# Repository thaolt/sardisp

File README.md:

# sardisp

## Content

  * [What is it?](#what-is-it)
  * [Installation](#installation)
    + [Windows](#windows)
    + [Linux](#linux)
  * [How to use](#how-to-use)
    + [avrdude](#avrdude)
    + [AVRDUDESS](#avrdudess)
    + [Arduino IDE](#arduino-ide)
  * [Tools](#tools)
  * [Schematic](#schematic)
  * [Perf-board implement](#perf-board-implement)
  * [References](#references)

## What is it?

DIY Simple Arduino In-System-Programmer (aka perf-board USBasp clone)

## Installation

### Windows

**Driver installation**

Please read:

* https://zadig.akeo.ie/
* https://electronics.stackexchange.com/questions/416714/avrdude-does-not-recognize-usbasp-device/417509#417509

Or download:

https://raw.githubusercontent.com/thaolt/sardisp/master/drivers/usbasp_signed.zip

### Linux

Linux doesn't need driver installation

However, it would be more convenient to allow current user access USB instead of execute commands under `root` or `sudo`

If you ever run these steps before, they don't need to be executed again

`$USER` is your current login name on your machine

```
sudo adduser $USER dialout
sudo adduser $USER tty
sudo adduser $USER plugdev
```

Then log out of current desktop session and log in again, it's done.

## How to use

Any software / IDE support USBasp programmer

### avrdude

```
avrdude -u -c usbasp -P usb ...
```
### AVRDUDESS

### Arduino IDE

`Tools` > `Programmer` > `USBasp`

## Tools

* **Kicad PCB** software is used for making perf-board design easier. https://kicad.org/
* **AVRDUDESS** is a GUI software for avrdude for flashing the firmware, works on Windows, Mac, Linux. https://blog.zakkemble.net/avrdudess-a-gui-for-avrdude/

## Schematic

## Perf-board implement

## References

* https://www.fischl.de/usbasp/
* https://github.com/obdev/v-usb
* https://hackaday.io/project/27401-creative-repairs-and-hacks/log/156127-replacing-an-atmega8-with-a-atmega328p-on-a-usbasp-board
* https://tiktakx.wordpress.com/tag/diy-usbasp-using-atmega-328/

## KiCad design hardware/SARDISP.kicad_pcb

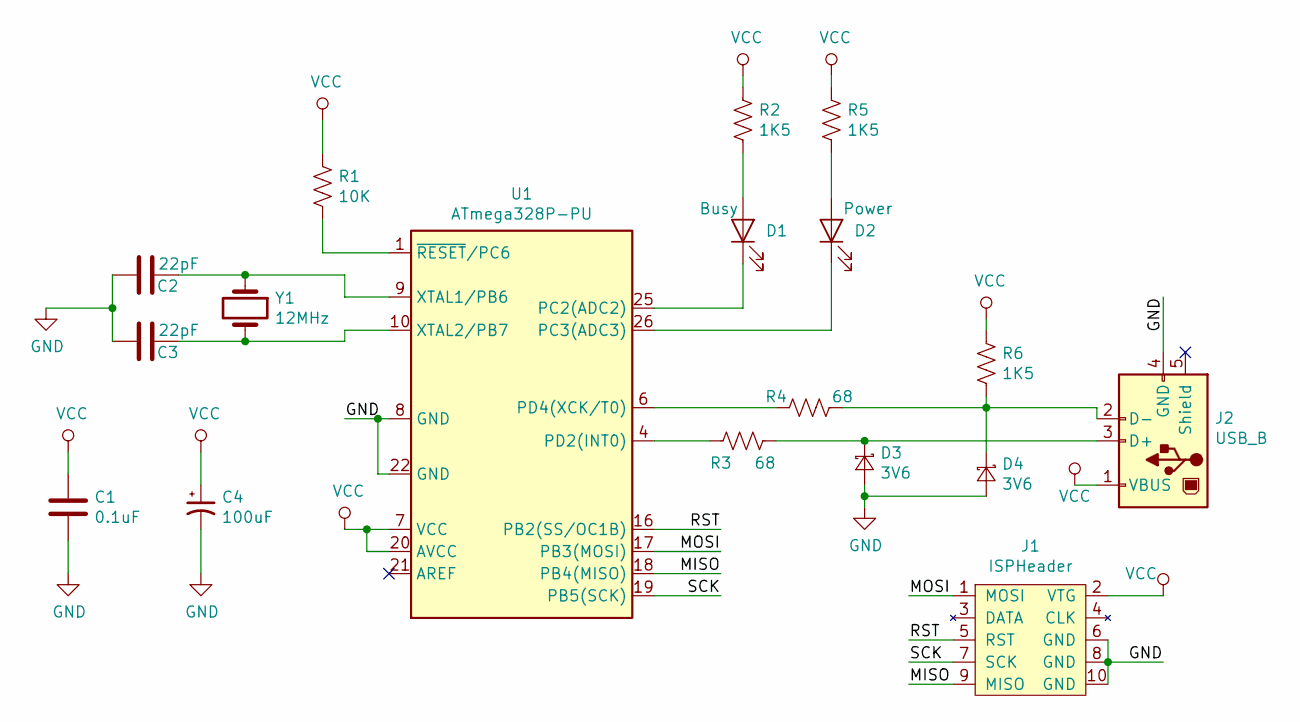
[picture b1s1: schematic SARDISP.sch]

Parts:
C1: 0.1uF; C_Disc_D3.0mm_W1.6mm_P2.50mm
C2, C3: 22pF; C_Disc_D3.0mm_W1.6mm_P2.50mm
C4: 100uF; CP_Radial_D5.0mm_P2.50mm
D1: Busy; LED_D3.0mm
D2: Power; LED_D3.0mm
D3, D4: 3V6; D_A-405_P7.62mm_Horizontal
J1: ISPHeader; IDC-Header_2x05_P2.54mm_Horizontal
J2: USB_B; USB_A_Stewart_SS-52100-001_Horizontal
R1: 10K; R_Axial_DIN0204_L3.6mm_D1.6mm_P7.62mm_Horizontal
R2, R5, R6: 1K5; R_Axial_DIN0204_L3.6mm_D1.6mm_P7.62mm_Horizontal
R3, R4: 68; R_Axial_DIN0204_L3.6mm_D1.6mm_P7.62mm_Horizontal
U1: ATmega328P-PU; DIP-28_W7.62mm
Y1: 12MHz; Crystal_HC18-U_Vertical

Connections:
/MISO: J1.9 (MISO), U1.18 (PB4(MISO))
/MOSI: J1.1 (MOSI), U1.17 (PB3(MOSI))
/RST: J1.5 (RST), U1.16 (PB2(SS/OC1B))
/SCK: J1.7 (SCK), U1.19 (PB5(SCK))
GND: C1.2, C2.2, C3.2, C4.2, D3.2 (A), D4.2 (A), J1.6 (GND), J1.8 (GND), J1.10 (GND), J2.4 (GND), U1.8 (GND), U1.22 (GND)
unnamed: C2.1, U1.9 (XTAL1/PB6), Y1.1
unnamed: C3.1, U1.10 (XTAL2/PB7), Y1.2
unnamed: D1.1 (K), U1.25 (PC2(ADC2))
unnamed: D1.2 (A), R2.2
unnamed: D2.1 (K), U1.26 (PC3(ADC3))
unnamed: D2.2 (A), R5.2
unnamed: D3.1 (K), J2.3 (D+), R3.1
unnamed: D4.1 (K), J2.2 (D-), R4.2, R6.2
unnamed: R1.2, U1.1 (~RESET~/PC6)
unnamed: R3.2, U1.4 (PD2(INT0))
unnamed: R4.1, U1.6 (PD4(XCK/T0))
VCC: C1.1, C4.1, J1.2 (VTG), J2.1 (VBUS), R1.1, R2.1, R5.1, R6.1, U1.7 (VCC), U1.20 (AVCC)

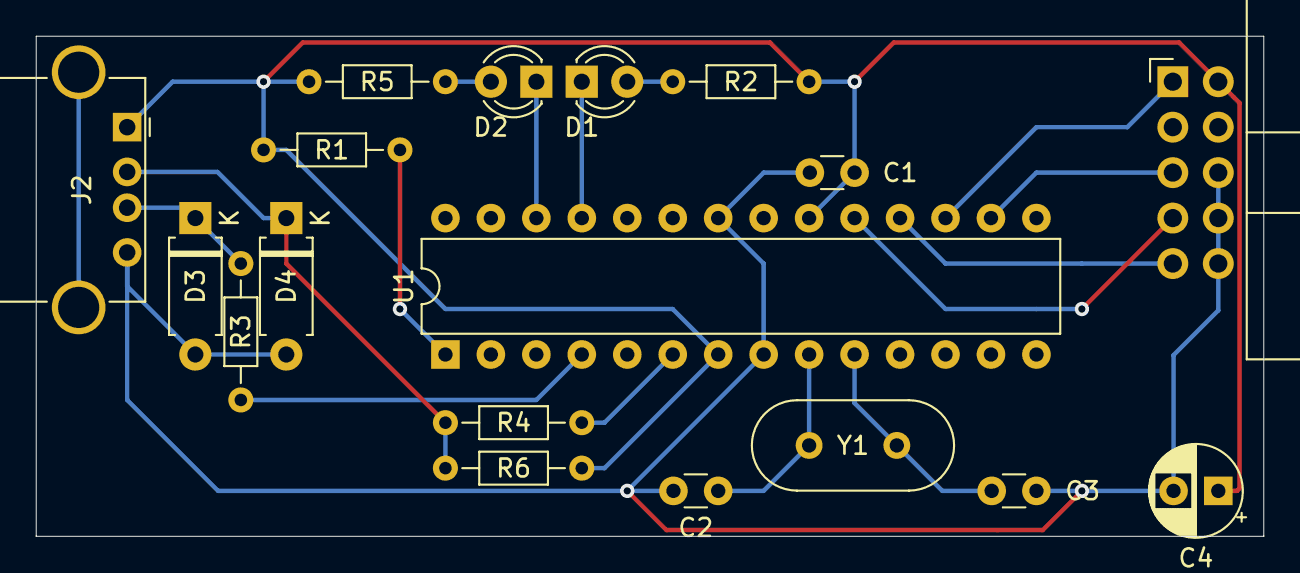
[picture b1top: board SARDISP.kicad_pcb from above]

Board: 2 copper layers, 68.6 x 27.9 mm, 18 parts (0 on the bottom side), 17 nets.

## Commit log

2021-02-09 intial commit
2021-02-09 Create LICENSE
2021-02-09 added pictures
2021-02-09 added windows signed drivers
2021-02-09 more pictures
